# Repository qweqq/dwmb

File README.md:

# dwmb
Dude, where's my bike?!

# Goals

Build a system that notifies you/a guard/a group of people if someone is trying to steal your bike! (and in case it is stolen provide information)

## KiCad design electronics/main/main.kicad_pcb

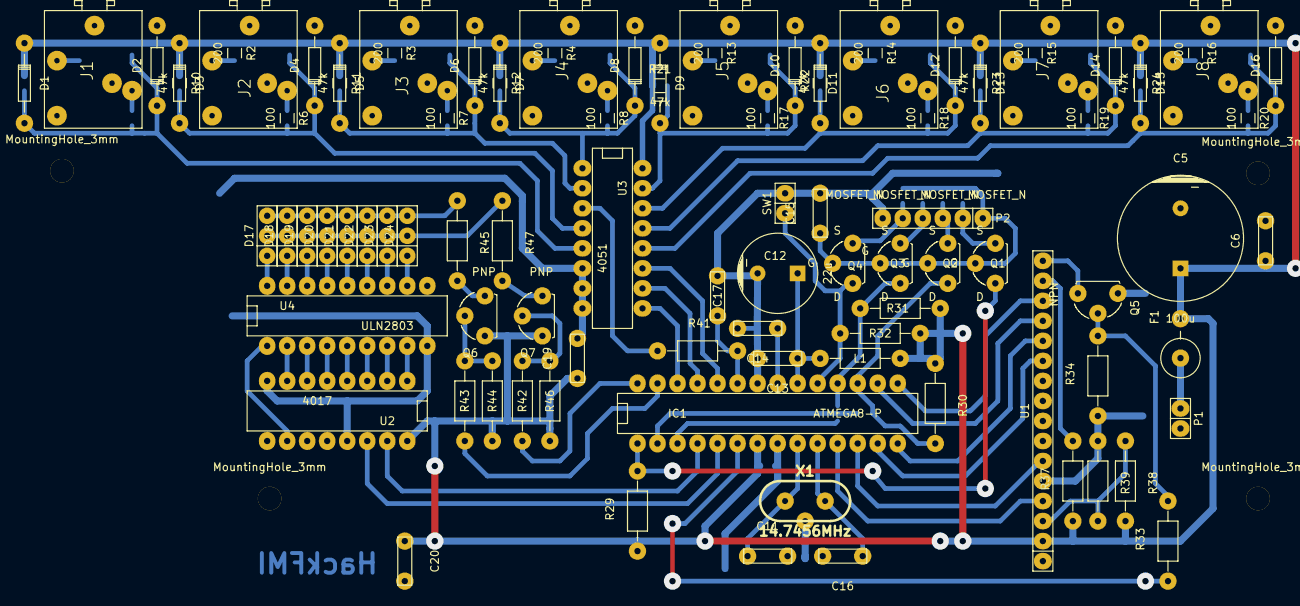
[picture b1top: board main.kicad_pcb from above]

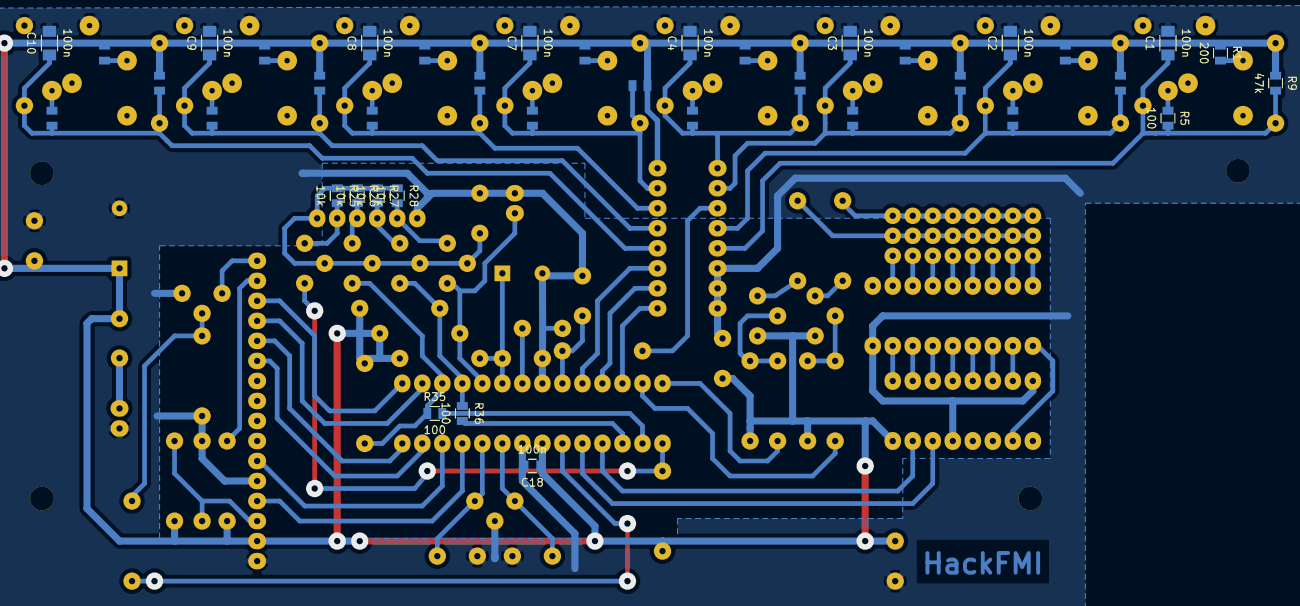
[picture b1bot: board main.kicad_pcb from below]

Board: 2 copper layers, 120 parts (18 on the bottom side), 84 nets.

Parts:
C1, C2, C3, C4, C7, C8, C9, C10: 100n; C_1206
C5: 100u; Capacitor16x25RM7.5
C6, C13, C14, C15, C17, C19, C20: 100n; Capacitor6MMDiscRM5
C11, C16: 22p; Capacitor6MMDiscRM5
C12: 22u; Capacitor10x16RM5
C18: 100n; C_0805
D1, D2, D3, D4, D5, D6, D7, D8, D9, D10, D11, D12, D13, D14, D15, D16: DIODE; Diode_DO-35_SOD27_Horizontal_RM10
D17, D18, D19, D20, D21, D22, D23, D24: BI_LED2; Pin_Header_Straight_1x03
F1: 700mA; Resistor_Vertical_RM5mm
IC1: ATMEGA8-P; DIP-28__300
J1, J2, J3, J4, J5, J6, J7, J8: CABLE; JACK_STEREO
L1: 470nH; Resistor_Horizontal_RM10mm
MountingHole_3mm, MountingHole_3mm#2, MountingHole_3mm#3, MountingHole_3mm#4: VAL**; MountingHole_3mm
P1: 5v; Pin_Header_Straight_1x02
P2: PI; Pin_Header_Straight_1x06
Q1, Q2, Q3, Q4: MOSFET_N; TO-92-FET-molded-wide-oval-DGS
Q5: NPN; TO-92-Free-molded-wide
Q6, Q7: PNP; TO-92-Free-molded-wide
R1, R2, R3, R4, R13, R14, R15, R16: 200; R_0805
R5, R6, R7, R8, R17, R18, R19, R20, R35, R36: 100; R_0805
R9, R10, R11, R12, R21, R22, R23, R24: 47k; R_0805
R25, R26, R27, R28: 10k; R_0805
R29, R30, R31, R32: 10k; Resistor_Horizontal_RM10mm
R33, R42, R43: 2.2k; Resistor_Horizontal_RM10mm
R34, R44, R46: 4.7k; Resistor_Horizontal_RM10mm
R37: 33; Resistor_Horizontal_RM10mm
R38: RC1; Resistor_Horizontal_RM10mm
R39: RC2; Resistor_Horizontal_RM10mm
R41: 50; Resistor_Horizontal_RM10mm
R45, R47: 100; Resistor_Horizontal_RM10mm
SW1: SW_PUSH; Pin_Header_Straight_1x02
U1: HD44780; Pin_Header_Straight_1x16
U2: 4017; DIP-16__300
U3: 4051; DIP-16__300
U4: ULN2803; DIP-18__300
X1: 14.7456MHz; HC-49V

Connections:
+3.3VP: C15.1, P2.1, Q1.G, Q2.G, Q3.G, Q4.G, R25.1, R26.1, R27.1, R28.1
/BACKLIGHT: IC1.6, R33.1
/IN1: C1.1, D1.1, D2.2, R5.2, R9.2, U3.5
/IN2: C2.1, D3.1, D4.2, R6.2, R10.2, U3.4
/IN3: C3.1, D5.1, D6.2, R7.2, R11.2, U3.2
/IN4: C4.1, D7.1, D8.2, R8.2, R12.2, U3.1
/IN5: C7.1, D9.1, D10.2, R17.2, R21.2, U3.15
/IN6: C8.1, D11.1, D12.2, R18.2, R22.2, U3.14
/IN7: C9.1, D13.1, D14.2, R19.2, R23.2, U3.13
/IN8: C10.1, D15.1, D16.2, R20.2, R24.2, U3.12
/L1: U2.1, U4.8
/L2: U2.2, U4.7
/L3: U2.3, U4.6
/L4: U2.4, U4.5
/L5: U2.5, U4.4
/L6: U2.6, U4.3
/L7: U2.7, U4.2
/L8: U2.10, U4.1
/LED_A1: IC1.28, R42.1
/LED_A2: IC1.27, R43.1
/LED_CLK: IC1.5, U2.14
/LED_RESET: IC1.4, U2.15
/MISO: IC1.18, Q3.D, R31.2, R36.1
/MOSI: IC1.17, Q2.D, R30.2, R35.1
/RESET: IC1.1, Q1.D, R29.2
/RX: IC1.2, R35.2
/SCK: IC1.19, Q4.D, R32.2, SW1.1
/TX: IC1.3, R36.2
GND: C1.2, C2.2, C3.2, C4.2, C5.2, C6.2, C7.2, C8.2, C9.2, C10.2, C11.2, C12.2, C13.2, C14.2, C15.2, C16.2, C17.2, C18.2, C19.2, C20.2, D2.1, D4.1, D6.1, D8.1, D10.1, D12.1, D14.1, D16.1, IC1.8, IC1.22, J1.1, J2.1, J3.1, J4.1, J5.1, J6.1, J7.1, J8.1, MountingHole_3mm.1, MountingHole_3mm#2.1, MountingHole_3mm#3.1, MountingHole_3mm#4.1, P1.2, P2.6, Q5.1, R34.1, R39.1, SW1.2, U1.1, U1.5, U2.8, U2.13, U3.6, U3.7, U3.8, U4.9, X1.0
unnamed: C11.1, IC1.9, X1.1
unnamed: C12.1, C13.1, IC1.20, L1.1
unnamed: C14.1, IC1.21
unnamed: C16.1, IC1.10, X1.2
unnamed: C17.1, IC1.23, R41.2
unnamed: D17.1, U4.18
unnamed: D17.2, D18.2, D19.2, D20.2, D21.2, D22.2, D23.2, D24.2, R47.1
unnamed: D17.3, D18.3, D19.3, D20.3, D21.3, D22.3, D23.3, D24.3, R45.1
unnamed: D18.1, U4.17
unnamed: D19.1, U4.16
unnamed: D20.1, U4.15
unnamed: D21.1, U4.14
unnamed: D22.1, U4.13
unnamed: D23.1, U4.12
unnamed: D24.1, U4.11
unnamed: F1.1, P1.1
unnamed: IC1.11, U1.4
unnamed: IC1.12, U1.6
unnamed: IC1.13, U1.11
unnamed: IC1.14, U1.12
unnamed: IC1.15, U1.14
unnamed: IC1.16, U1.13
unnamed: IC1.24, U3.11
unnamed: IC1.25, U3.10
unnamed: IC1.26, U3.9
unnamed: J1.3, R1.2
unnamed: J1.4, R5.1
unnamed: J2.3, R2.2
unnamed: J2.4, R6.1
unnamed: J3.3, R3.2
unnamed: J3.4, R7.1
unnamed: J4.3, R4.2
unnamed: J4.4, R8.1
unnamed: J5.3, R13.2
unnamed: J5.4, R17.1
unnamed: J6.3, R14.2
unnamed: J6.4, R18.1
unnamed: J7.3, R15.2
unnamed: J7.4, R19.1
unnamed: J8.3, R16.2
unnamed: J8.4, R20.1
unnamed: P2.2, Q1.S, R25.2
unnamed: P2.3, Q2.S, R26.2
unnamed: P2.4, Q3.S, R27.2
unnamed: P2.5, Q4.S, R28.2
unnamed: Q5.2, R33.2, R34.2
unnamed: Q5.3, U1.16
unnamed: Q6.2, R43.2, R44.1
unnamed: Q6.3, R45.2
unnamed: Q7.2, R42.2, R46.1
unnamed: Q7.3, R47.2
unnamed: R37.2, U1.15
unnamed: R38.1, R39.2, U1.3
unnamed: R41.1, U3.3
VCC: C5.1, C6.1, C18.1, C19.1, C20.1, D1.2, D3.2, D5.2, D7.2, D9.2, D11.2, D13.2, D15.2, F1.2, IC1.7, L1.2, Q6.1, Q7.1, R1.1, R2.1, R3.1, R4.1, R9.1, R10.1, R11.1, R12.1, R13.1, R14.1, R15.1, R16.1, R21.1, R22.1, R23.1, R24.1, R29.1, R30.1, R31.1, R32.1, R37.1, R38.2, R44.2, R46.2, U1.2, U2.16, U3.16

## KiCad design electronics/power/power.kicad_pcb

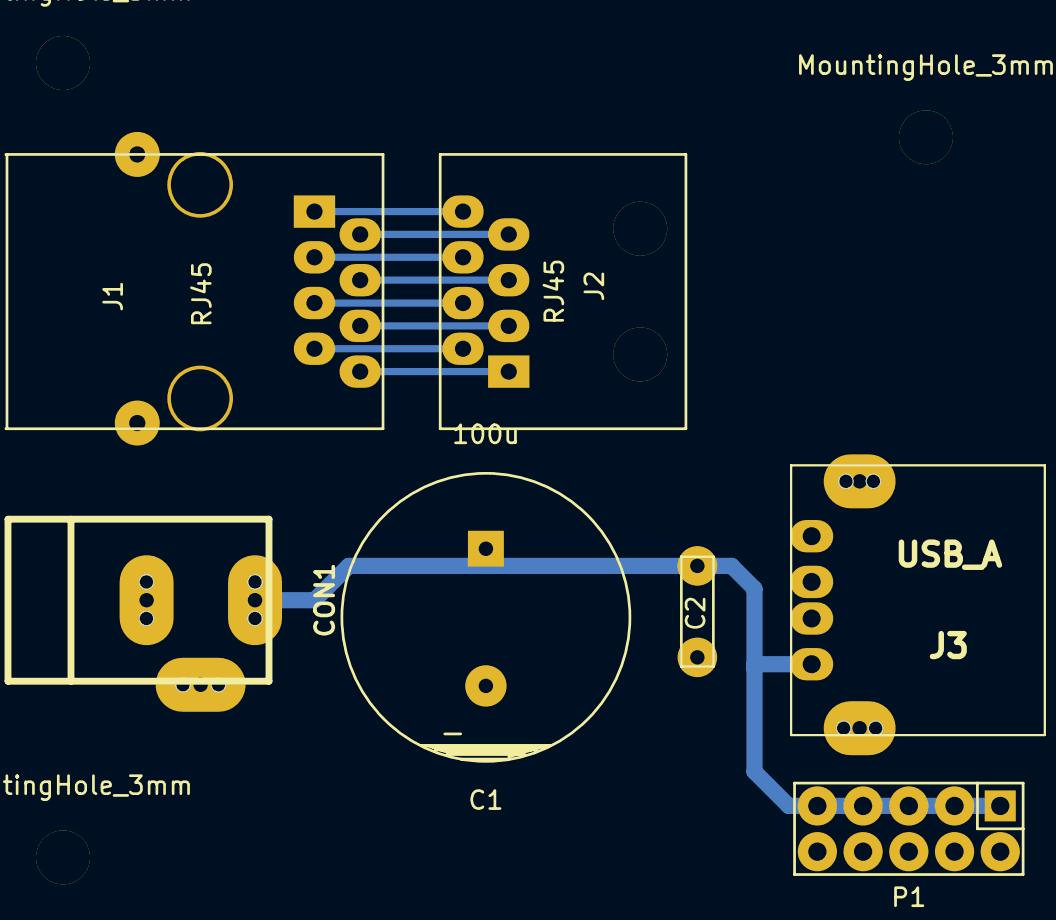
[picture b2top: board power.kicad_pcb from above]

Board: 2 copper layers, 10 parts (0 on the bottom side), 10 nets.

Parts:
C1: 100u; Capacitor16x25RM7.5
C2: 100n; Capacitor6MMDiscRM5
CON1: 5V; BARREL_JACK
J1: RJ45; RJ45_8_BIG
J2: RJ45; RJ45_SOLDER
J3: USB_A
MountingHole_3mm, MountingHole_3mm#2, MountingHole_3mm#3: VAL**; MountingHole_3mm
P1: CONN_02X05; Pin_Header_Straight_2x05

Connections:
/+5v: C1.1, C2.1, CON1.1, J3.1, P1.1, P1.3, P1.5, P1.7, P1.9
GND: C1.2, C2.2, CON1.2, CON1.3, J1.9, J1.Hole, J3.4, J3.5, J3.6, MountingHole_3mm.1, MountingHole_3mm#2.1, MountingHole_3mm#3.1, P1.2, P1.4, P1.6, P1.8, P1.10
unnamed: J1.1, J2.8
unnamed: J1.2, J2.7
unnamed: J1.3, J2.6
unnamed: J1.4, J2.5
unnamed: J1.5, J2.4
unnamed: J1.6, J2.3
unnamed: J1.7, J2.2
unnamed: J1.8, J2.1

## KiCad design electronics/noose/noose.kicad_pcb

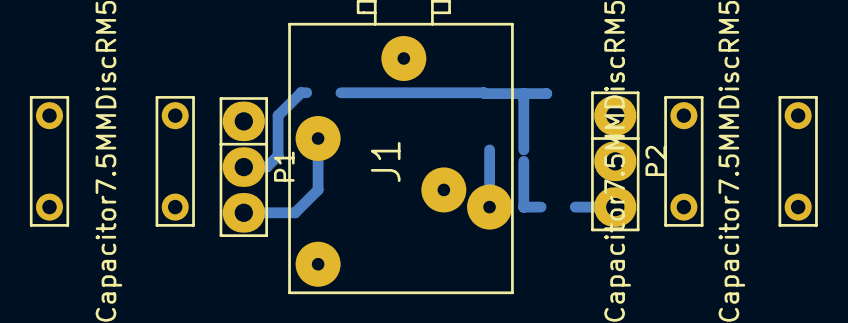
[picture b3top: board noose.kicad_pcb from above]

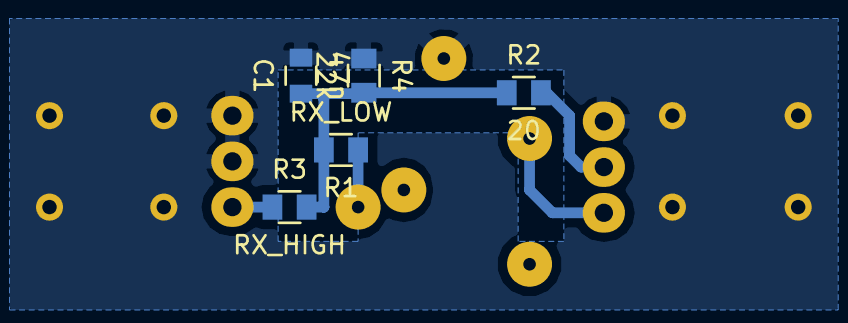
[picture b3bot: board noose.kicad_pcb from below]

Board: 2 copper layers, 12 parts (5 on the bottom side), 6 nets.

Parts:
C1: 47n; C_0805
Capacitor7.5MMDiscRM5, Capacitor7.5MMDiscRM5#2, Capacitor7.5MMDiscRM5#3, Capacitor7.5MMDiscRM5#4: VAL**; Capacitor7.5MMDiscRM5
J1: JACK; JACK_STEREO
P1: IN_CABLE; Pin_Header_Straight_1x03
P2: NOOSE_CABLE; Pin_Header_Straight_1x03
R1: RX_LOW; R_0805
R2: 20; R_0805
R3: RX_HIGH; R_0805
R4: 22k; R_0805

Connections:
GND: C1.2, Capacitor7.5MMDiscRM5.1, Capacitor7.5MMDiscRM5.2, Capacitor7.5MMDiscRM5#2.1, Capacitor7.5MMDiscRM5#2.2, Capacitor7.5MMDiscRM5#3.1, Capacitor7.5MMDiscRM5#3.2, Capacitor7.5MMDiscRM5#4.1, Capacitor7.5MMDiscRM5#4.2, J1.1, P1.1, P2.1, P2.2, R4.1
unnamed: C1.1, R1.2, R2.1, R3.2, R4.2
unnamed: J1.3, P1.3
unnamed: J1.4, R1.1
unnamed: P1.2, R2.2
unnamed: P2.3, R3.1

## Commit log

2015-11-29 add noose kicad project and draw a schematic symbol for female jack
2015-11-29 finish drawing the noose schematic
2015-11-29 finish drawing noose schematic
2015-11-29 add main board with mega8
2015-11-29 draw lcd display symbol
2015-11-30 move compontents to separate folder
2015-11-30 draw some more stuff on the main schematic
2015-12-01 use a correct counter ic
2015-12-01 draw voltage translation step and ADC power filter
2015-12-01 add crystal models
2015-12-01 add crystal and power connector
2015-12-01 fix ERC errors
2015-12-02 some minor fixes on the schematic
2015-12-02 add a pdf of the schematic
2015-12-02 fix wrong values on resistors
2015-12-02 replace avr with correct footprint
2015-12-02 add some footprints
2015-12-03 add pcb
2015-12-03 remove backup
2015-12-03 ignore backups
2015-12-03 draw inputs on pcb
2015-12-03 draw led control
2015-12-03 draw some more of the pcb
2015-12-03 add some ground
2015-12-03 now remain vcc and gnd
2015-12-04 fucking reset pin
2015-12-04 looks finished
2015-12-04 move jacks to components folder
2015-12-04 add mounting holes
2015-12-04 add noose pcb
2015-12-04 draw pcb for noose
2015-12-04 add power schematic
2015-12-04 add barrel jack and rj45 connector
2015-12-04 draw power schematic
2015-12-04 draw power pcb
2015-12-04 plot boards
2015-12-04 add printouts
2015-12-04 fix borders of main board
2015-12-04 move printout files
2015-12-18 add basic gitignore
2015-12-18 add basic avr code
2015-12-18 add some go cross-compiling code
2015-12-18 add electronic schematics and pcb's
2015-12-18 add rfid reader code
2015-12-18 add stupid build script for rfid reader
2015-12-18 rename rfid reader
2015-12-18 Add server stuff and database foos
2015-12-19 write some avr boilerplate
2015-12-19 implement measuring of voltages
2015-12-19 Server catches errors with hole state change
2015-12-19 Poop! supposed to work now
2015-12-19 implement communication between avr and the go code
2015-12-19 add adc clamp values
2015-12-19 initial ui stuff
2015-12-19 fix comments
2015-12-19 asdfasdf
2015-12-19 Logo.
2015-12-19 img folder + initial js
2015-12-19 empty folders :D
2015-12-19 Pooper works
2015-12-19 state detection works!
2015-12-19 change cardid to rfid
2015-12-19 Add trafic light.
2015-12-19 implement requests to server
2015-12-19 implement rfid reader
2015-12-19 implement rfid hashing
2015-12-19 requests work!
2015-12-19 implement LCD control
2015-12-19 wtf did I just do?!
2015-12-19 processing responses works!
2015-12-19 display messages from responses on LCD
2015-12-19 Poop and alive work
2015-12-19 Test files work
2015-12-19 fix message handling
2015-12-19 Poop and alive work. Alert message if device unreachable
2015-12-19 stuff
2015-12-19 implement display timeouts
2015-12-19 fix all messages
2015-12-19 progress
2015-12-19 asdf
2015-12-19 implement led control
2015-12-19 implement led control in go
2015-12-19 Alarm turns off when user unpoops. Test work with slots
2015-12-19 Textures
2015-12-20 first tries for lights logic
2015-12-20 fixes
2015-12-20 fix /status
2015-12-20 remove /status_all
2015-12-20 js fixes
2015-12-20 fix typos
2015-12-20 make /status get request
2015-12-20 change on to off in /status
2015-12-20 added gitignore
2015-12-20 remove database.db
2015-12-20 ignore *.pyc files
2015-12-20 html + css changes
2015-12-20 Translate Hristo's python to ruby
2015-12-20 reformat messages to avr to allow setting leds
2015-12-20 Server can now return events and time
2015-12-20 implement led messages
2015-12-20 Search return array of hash
2015-12-20 fix dodo reported test
2015-12-20 fix merge
2015-12-20 all led stuff is done
2015-12-20 Try to fix timer
2015-12-20 loged user header
2015-12-20 css changes
2015-12-20 fix stop error bug
2015-12-20 Add alarm sound
2015-12-20 Add attr_accessor
2015-12-20 implement sound player
2015-12-20 css stuff
2015-12-20 Poop sound
2015-12-20 added dummy mail code
2015-12-20 Remove shitty cable
2015-12-20 wtf did I do there? why did build do that?!
2015-12-20 css fixes
2015-12-20 implement snapshot sending
2015-12-20 styles
2015-12-20 js fuctionalities - cookies, session, requests to server, login
2015-12-20 Server images and emails
2015-12-20 Other alarm sound
2015-12-20 alarm sound now works
2015-12-20 Try catch the email error
2015-12-20 new poop sound
2015-12-20 separate form from buttons
2015-12-20 pics
2015-12-20 mm workarounds!
2015-12-20 fix sound
2015-12-20 make it real
2015-12-20 asdlfalsdfl
2015-12-20 Main.js
2015-12-20 blah
2015-12-20 alalal
2015-12-20 lalala
2015-12-20 Fix server
2015-12-20 asdmkfajsdjfajsdf
2015-12-20 tooltips
2015-12-20 removes minus for slots
2015-12-24 remove flat copy of electronics folder
2015-12-24 add MIT license
2015-12-24 fix gitignore
